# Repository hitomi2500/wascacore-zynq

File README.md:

# wascacore-zynq
Core board module for wasca cartridge, zynq flavour.

Zynq and DDR routing from [`Stanlazy/7z010_ddr`][1].

SODIMM 200 cart edge and board outline from [`Wallbraker/SODIMM`][2].

[1]: https://github.com/Stanlazy/7z010_ddr
[2]: https://github.com/Wallbraker/SODIMM

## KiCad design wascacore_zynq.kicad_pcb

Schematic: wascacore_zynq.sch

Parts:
C1, C2, C21, C23, C42, C43, C44, C45, C46, C47, C48, C49, C51, C52, C53, C54, C56, C57, C58, C59, C60, C61, C62, C63, C64, C65, C66, C67, C68, C69, C70, C71, C72, C73: 0.1uF; C_0603_1608Metric_Pad1.05x0.95mm_HandSolder
C3, C4, C5, C6, C7, C9, C10, C11, C12, C13, C15, C16, C17, C18, C19, C20, C25, C27, C28, C29, C30, C32, C34, C37, C38, C39: C; C_0201_0603Metric
C8, C14, C24, C31, C36, C40, C41: C; C_0402_1005Metric
C22, C26, C33, C35: C; C_0201_0603Metric_WideGap
C50: 10uF; C_1206_HandSoldering
C55: 4.7uF; C_0603_1608Metric_Pad1.05x0.95mm_HandSolder
CN1, CN3: Conn_02x02_Odd_Even; PinHeader_2x02_P2.54mm_Vertical
CN2: Conn_02x05_Odd_Even; Multicomp_MC9A22-1034_2x05_P2.54mm_Horizontal
CN4: Conn_02x03_Odd_Even; PinHeader_2x03_P2.54mm_Vertical
CN5: USB_C_Receptacle_USB2.0; DX07S016JA1R1500
D1: LED_RGB; LED_RGB_5050-6
D2: LED_BCGR; LED_D5.0mm-4_RGB
D3: LED; LED_D3.0mm
D4: BAT54C; SOT-23
IC1: SDRAM_MT48_x16; TSOP-II-54_22.2x10.16mm_P0.8mm
J1: SODIMM-200; SODIMM_DDR2_EDGE
R1: 1K; C_0603_1608Metric_Pad1.05x0.95mm_HandSolder
R2: 0; C_0603_1608Metric_Pad1.08x0.95mm_HandSolder
R3, R4, R17: 10K; C_0603_1608Metric_Pad1.05x0.95mm_HandSolder
R5, R12, R13: 80Ω; R_0201_0603Metric
R6: 4K7Ω; R_0201_0603Metric
R7: 240Ω; R_0201_0603Metric
R8, R9, R10, R11: 470; C_0603_1608Metric_Pad1.08x0.95mm_HandSolder
R14: 470; C_0603_1608Metric_Pad1.05x0.95mm_HandSolder
R15: 5K1; C_0603_1608Metric_Pad1.08x0.95mm_HandSolder
R16: 4K7; C_0603_1608Metric_Pad1.05x0.95mm_HandSolder
RN1, RN2, RN3, RN4, RN5, RN6: 40Ω; R_Array_Convex_4x0402
U1, U2, U5, U6, U7: SN74LVC1T45DBV; SOT-23-6
U3: DDR3; BGA-96_9.0x13.0mm_Layout2x3x16_P0.8mm_NoPaste
U4: xc7z010clg400
U8: LD1117S33TR_SOT223; SOT-223-3_TabPin2

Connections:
/5V: J1.2, J1.4, J1.6, J1.8, J1.10, J1.12
/5V_SATURN_DETECT: R8.2
/+3_3V: C21.1, C23.1, C45.1, C46.1, C47.1, C49.1, C50.1, C51.1, C53.1, C56.1, C57.1, C58.1, C59.1, C60.1, C61.1, C62.1, C63.1, C64.1, C65.1, C66.1, C67.1, C68.1, C69.1, C70.1, C71.1, C72.1, C73.1, CN1.2, CN2.4, CN3.2, CN4.1, IC1.1 (VDD), IC1.3 (VDD), IC1.9 (VDD), IC1.14 (VDD), IC1.27 (VDD), IC1.43 (VDD), IC1.49 (VDD), R3.1, R4.1, U1.1 (VCCA), U2.1 (VCCA), U5.1 (VCCA), U5.5 (DIR), U6.1 (VCCA), U6.5 (DIR), U7.1 (VCCA), U7.5 (DIR), U8.2 (VO); also elsewhere on the board
/+5V_SATURN: C1.1, C2.1, C42.1, C43.1, C44.1, D4.1, R8.1, U1.6 (VCCB), U2.6 (VCCB), U5.6 (VCCB), U6.6 (VCCB), U7.6 (VCCB)
/+5V_SYS: C48.1, CN1.4, D4.3, U8.3 (VI)
/+5V_USB: C52.1, C54.1, C55.1, CN5.A4 (VBUS), CN5.A9 (VBUS), CN5.B4 (VBUS), CN5.B9 (VBUS), D4.2, R16.2
/ABUS_IRQ: U1.4 (B)
/DBG_UART_RX: CN4.5
/DBG_UART_TX: CN4.6
/DDR_VRN: R12.1, U4.G5 (PS_DDR_VRN_502)
/DDR_VRP: R13.1, U4.H5 (PS_DDR_VRP_502)
/DDR_ZQ0: R7.2, U3.L8 (ZQ)
/IBCK: U6.4 (B)
/IBCK_3V: U6.3 (A)
/ILRCK: U7.4 (B)
/ILRCK_3V: U7.3 (A)
/ISD: U5.4 (B)
/ISD_3V: U5.3 (A)
/JTAG_TCK: CN2.1, R1.1
/JTAG_TDI: CN2.9, R4.2
/JTAG_TMS: CN2.5, R3.2
/LED3: D3.2 (A)
/LEDB: R11.1
/LEDG: R10.1
/LEDR: R9.1
/SDR_A0: IC1.23 (A0), U4.D19 (IO_L4P_T0_35)
/SDR_A1: IC1.24 (A1), U4.D20 (IO_L4N_T0_35)
/SDR_A2: IC1.25 (A2), U4.E17 (IO_L3P_T0_DQS_AD1P_35)
/SDR_A3: IC1.26 (A3), U4.D18 (IO_L3N_T0_DQS_AD1N_35)
/SDR_A4: IC1.29 (A4), U4.H17 (IO_L13N_T2_MRCC_35)
/SDR_A5: IC1.30 (A5), U4.H16 (IO_L13P_T2_MRCC_35)
/SDR_A6: IC1.31 (A6), U4.H18 (IO_L14N_T2_AD4N_SRCC_35)
/SDR_A7: IC1.32 (A7), U4.J18 (IO_L14P_T2_AD4P_SRCC_35)
/SDR_A8: IC1.33 (A8), U4.F20 (IO_L15N_T2_DQS_AD12N_35)
/SDR_A9: IC1.34 (A9), U4.F19 (IO_L15P_T2_DQS_AD12P_35)
/SDR_A10: IC1.22 (A10), U4.E19 (IO_L5N_T0_AD9N_35)
/SDR_A11: IC1.35 (A11), U4.G18 (IO_L16N_T2_35)
/SDR_A12: IC1.36 (A12), U4.G17 (IO_L16P_T2_35)
/SDR_BA0: IC1.20 (BA0), U4.F17 (IO_L6N_T0_VREF_35)
/SDR_BA1: IC1.21 (BA1), U4.E18 (IO_L5P_T0_AD9P_35)
/SDR_CAS: IC1.17 (nCAS), U4.M19 (IO_L7P_T1_AD2P_35)
/SDR_CKE: IC1.37 (CKE), U4.L15 (IO_L22N_T3_AD7N_35)
/SDR_CLK: IC1.38 (CLK), U4.N15 (IO_L21P_T3_DQS_AD14P_35)
/SDR_CS: IC1.19 (nCS), U4.F16 (IO_L6P_T0_35)
/SDR_DQ0: IC1.2 (DQ0), U4.K17 (IO_L12P_T1_MRCC_35)
/SDR_DQ1: IC1.4 (DQ1), U4.K18 (IO_L12N_T1_MRCC_35)
/SDR_DQ2: IC1.5 (DQ2), U4.L16 (IO_L11P_T1_SRCC_35)
/SDR_DQ3: IC1.7 (DQ3), U4.L17 (IO_L11N_T1_SRCC_35)
/SDR_DQ4: IC1.8 (DQ4), U4.K19 (IO_L10P_T1_AD11P_35)
/SDR_DQ5: IC1.10 (DQ5), U4.J19 (IO_L10N_T1_AD11N_35)
/SDR_DQ6: IC1.11 (DQ6), U4.L19 (IO_L9P_T1_DQS_AD3P_35)
/SDR_DQ7: IC1.13 (DQ7), U4.L20 (IO_L9N_T1_DQS_AD3N_35)
/SDR_DQ8: IC1.42 (DQ8), U4.K14 (IO_L20P_T3_AD6P_35)
/SDR_DQ9: IC1.44 (DQ9), U4.J14 (IO_L20N_T3_AD6N_35)
/SDR_DQ10: IC1.45 (DQ10), U4.H15 (IO_L19P_T3_35)
/SDR_DQ11: IC1.47 (DQ11), U4.G15 (IO_L19N_T3_VREF_35)
/SDR_DQ12: IC1.48 (DQ12), U4.G19 (IO_L18P_T2_AD13P_35)
/SDR_DQ13: IC1.50 (DQ13), U4.G20 (IO_L18N_T2_AD13N_35)
/SDR_DQ14: IC1.51 (DQ14), U4.J20 (IO_L17P_T2_AD5P_35)
/SDR_DQ15: IC1.53 (DQ15), U4.H20 (IO_L17N_T2_AD5N_35)
/SDR_DQMH: IC1.39 (UDQM-DQMH), U4.N16 (IO_L21N_T3_DQS_AD14N_35)
/SDR_DQML: IC1.15 (LDQM-DQML), U4.M17 (IO_L8P_T1_AD10P_35)
/SDR_RAS: IC1.18 (nRAS), U4.M20 (IO_L7N_T1_AD2N_35)
/SDR_WE: IC1.16 (nWE), U4.M18 (IO_L8N_T1_AD10N_35)
/SSEL: U2.4 (B)
/SWCLK: CN3.3
/SWDIO: CN3.1
/VBUS_SENSE: R16.1, R17.2
DDR_A0: RN4.7 (R2.2), U3.N3 (A0), U4.N2 (PS_DDR_A0_502)
DDR_A1: RN3.8 (R1.2), U3.P7 (A1), U4.K2 (PS_DDR_A1_502)
DDR_A2: RN4.6 (R3.2), U3.P3 (A2), U4.M3 (PS_DDR_A2_502)
DDR_A3: RN2.5 (R4.2), U3.N2 (A3), U4.K3 (PS_DDR_A3_502)
DDR_A4: RN5.6 (R3.2), U3.P8 (A4), U4.M4 (PS_DDR_A4_502)
DDR_A5: RN3.5 (R4.2), U3.P2 (A5), U4.L1 (PS_DDR_A5_502)
DDR_A6: RN4.8 (R1.2), U3.R8 (A6), U4.L4 (PS_DDR_A6_502)
DDR_A7: RN3.6 (R3.2), U3.R2 (A7), U4.K4 (PS_DDR_A7_502)
DDR_A8: RN3.7 (R2.2), U3.T8 (A8), U4.K1 (PS_DDR_A8_502)
DDR_A9: RN1.7 (R2.2), U3.R3 (A9), U4.J4 (PS_DDR_A9_502)
DDR_A10: RN1.5 (R4.2), U3.L7 (A10/AP), U4.F5 (PS_DDR_A10_502)
DDR_A11: RN2.6 (R3.2), U3.R7 (A11), U4.G4 (PS_DDR_A11_502)
DDR_A12: RN2.8 (R1.2), U3.N7 (A12/~BC), U4.E4 (PS_DDR_A12_502)
DDR_A13: RN1.8 (R1.2), U3.T3 (A13), U4.D4 (PS_DDR_A13_502)
DDR_A14: RN2.7 (R2.2), U3.T7 (A14), U4.F4 (PS_DDR_A14_502)
DDR_BA0: RN5.8 (R1.2), U3.M2 (BA0), U4.L5 (PS_DDR_BA0_502)
DDR_BA1: RN6.7 (R2.2), U3.N8 (BA1), U4.R4 (PS_DDR_BA1_502)
DDR_BA2: RN1.6 (R3.2), U3.M3 (BA2), U4.J5 (PS_DDR_BA2_502)
DDR_CK+: R5.1, U3.J7 (CK), U4.L2 (PS_DDR_CKP_502)
DDR_CK-: R5.2, U3.K7 (~CK), U4.M2 (PS_DDR_CKN_502)
DDR_CKE: RN5.7 (R2.2), U3.K9 (CKE), U4.N3 (PS_DDR_CKE_502)
DDR_DQ0: U3.H8 (DQ5), U4.C3 (PS_DDR_DQ0_502)
DDR_DQ1: U3.F2 (DQ2), U4.B3 (PS_DDR_DQ1_502)
DDR_DQ2: U3.G2 (DQ6), U4.A2 (PS_DDR_DQ2_502)
DDR_DQ3: U3.H3 (DQ4), U4.A4 (PS_DDR_DQ3_502)
DDR_DQ4: U3.F7 (DQ1), U4.D3 (PS_DDR_DQ4_502)
DDR_DQ5: U3.E3 (DQ0), U4.D1 (PS_DDR_DQ5_502)
DDR_DQ6: U3.H7 (DQ7), U4.C1 (PS_DDR_DQ6_502)
DDR_DQ7: U3.F8 (DQ3), U4.E1 (PS_DDR_DQ7_502)
DDR_DQ8: U3.C2 (DQ11), U4.E2 (PS_DDR_DQ8_502)
DDR_DQ9: U3.A2 (DQ13), U4.E3 (PS_DDR_DQ9_502)
DDR_DQ10: U3.A3 (DQ15), U4.G3 (PS_DDR_DQ10_502)
DDR_DQ11: U3.C3 (DQ9), U4.H3 (PS_DDR_DQ11_502)
DDR_DQ12: U3.A7 (DQ12), U4.J3 (PS_DDR_DQ12_502)
DDR_DQ13: U3.D7 (DQ8), U4.H2 (PS_DDR_DQ13_502)
DDR_DQ14: U3.B8 (DQ14), U4.H1 (PS_DDR_DQ14_502)
DDR_DQ15: U3.C8 (DQ10), U4.J1 (PS_DDR_DQ15_502)
DDR_DQM0: U3.E7 (LDM), U4.A1 (PS_DDR_DM0_502)
DDR_DQM1: U3.D3 (UDM), U4.F1 (PS_DDR_DM1_502)
DDR_DQS0+: U3.F3 (LDQS), U4.C2 (PS_DDR_DQS_P0_502)
DDR_DQS0-: U3.G3 (~LDQS), U4.B2 (PS_DDR_DQS_N0_502)
DDR_DQS1+: U3.C7 (UDQS), U4.G2 (PS_DDR_DQS_P1_502)
DDR_DQS1-: U3.B7 (~UDQS), U4.F2 (PS_DDR_DQS_N1_502)
DDR_ODT: RN6.6 (R3.2), U3.K1 (ODT), U4.N5 (PS_DDR_ODT_502)
DDR_nCAS: RN6.5 (R4.2), U3.K3 (~CAS), U4.P5 (PS_DDR_CAS_B_502)
DDR_nCS: RN4.5 (R4.2), U3.L2 (~CS), U4.N1 (PS_DDR_CS_B_502)
DDR_nRAS: RN5.5 (R4.2), U3.J3 (~RAS), U4.P4 (PS_DDR_RAS_B_502)
DDR_nRST: R6.1, U3.T2 (~RESET), U4.B4 (PS_DDR_DRST_B_502)
DDR_nWE: RN6.8 (R1.2), U3.L3 (~WE), U4.M5 (PS_DDR_WE_B_502)
GND: C1.2, C2.2, C3.2, C4.2, C5.2, C6.2, C7.2, C8.2, C9.2, C10.2, C11.2, C12.2, C13.2, C14.2, C15.2, C16.2, C17.2, C18.2, C19.2, C20.2, C21.2, C22.2, C23.2, C24.2, C25.2, C26.2, C27.2, C28.2, C29.2, C30.2, C31.2, C32.2, C33.2, C34.2, C35.2, C36.2, C37.2, C38.2, C39.2, C40.2, C41.2, C42.2, C43.2, C44.2, C45.2, C46.2, C47.2, C48.2, C49.2, C50.2, C51.2, C52.2, C53.2, C54.2, C55.2, C56.2, C57.2, C58.2, C59.2, C60.2, C61.2, C62.2, C63.2, C64.2, C65.2, C66.2, C67.2, C68.2, C69.2, C70.2, C71.2, C72.2, C73.2, CN1.1, CN1.3, CN2.2, CN2.10, CN3.4, CN4.2, CN4.4, CN5.A1 (GND), CN5.A12 (GND), CN5.B1 (GND), CN5.B12 (GND), CN5.S1 (SHIELD), D1.1 (RK), D1.2 (GK), D1.3 (BK), D2.2 (K), IC1.6 (GND), IC1.12 (GND), IC1.28 (GND), IC1.41 (GND), IC1.46 (GND), IC1.52 (GND), IC1.54 (GND), J1.1, J1.3, J1.5, J1.7, J1.9, J1.11, J1.39, J1.40, J1.55, J1.56, J1.105, J1.106, J1.107, J1.108, J1.157, J1.158, J1.199, J1.200, R1.2, R6.2, R7.1, R13.2, R14.2, R15.1, R17.1, U1.2 (GND), U2.2 (GND), U2.5 (DIR), U3.A9 (VSS), U3.B1 (VSSQ), U3.B3 (VSS), U3.B9 (VSSQ), U3.D1 (VSSQ), U3.D8 (VSSQ), U3.E1 (VSS), U3.E2 (VSSQ), U3.E8 (VSSQ), U3.F9 (VSSQ), U3.G1 (VSSQ), U3.G8 (VSS), U3.G9 (VSSQ), U3.J2 (VSS), U3.J8 (VSS), U3.M1 (VSS), U3.M9 (VSS), U3.P1 (VSS), U3.P9 (VSS), U3.T1 (VSS), U3.T9 (VSS), U4.A8 (GND[59]), U4.A18 (GND[59]), U4.B1 (GND[59]), U4.B11 (GND[59]), U4.C4 (GND[59]), U4.C9 (GND[59]), U4.C14 (GND[59]), U4.D17 (GND[59]), U4.E10 (GND[59]), U4.E20 (GND[59]), U4.F3 (GND[59]), U4.F7 (GND[59]), U4.G10 (GND[59]), U4.G12 (GND[59]), U4.G16 (GND[59]), U4.H7 (GND[59]), U4.H9 (GND[59]), U4.H11 (GND[59]), U4.H13 (GND[59]), U4.H19 (GND[59]), U4.J2 (GND[59]), U4.J8 (GND[59]), U4.J12 (GND[59]), U4.K5 (GND[59]), U4.K7 (GND[59]), U4.K11 (GND[59]), U4.K13 (GND[59]), U4.K15 (GND[59]), U4.L8 (GND[59]), U4.L12 (GND[59]), U4.L18 (GND[59]), U4.M1 (GND[59]), U4.M7 (GND[59]), U4.M11 (GND[59]), U4.M13 (GND[59]), U4.N4 (GND[59]), U4.N8 (GND[59]), U4.N10 (GND[59]), U4.N12 (GND[59]), U4.N14 (GND[59]), U4.P7 (GND[59]), U4.P9 (GND[59]), U4.P11 (GND[59]), U4.P13 (GND[59]), U4.P17 (GND[59]), U4.R8 (GND[59]), U4.R12 (GND[59]), U4.R20 (GND[59]), U4.T3 (GND[59]), U4.T7 (GND[59]), U4.T13 (GND[59]), U4.U6 (GND[59]), U4.U16 (GND[59]), U4.V9 (GND[59]), U4.V19 (GND[59]), U4.W2 (GND[59]), U4.W12 (GND[59]), U4.Y5 (GND[59]), U4.Y15 (GND[59]), U5.2 (GND), U6.2 (GND), U7.2 (GND), U8.1 (GND); also elsewhere on the board
unnamed: CN5.A5 (CC1), CN5.B5 (CC2), R15.2
unnamed: CN5.A6 (D+), CN5.B6 (D+)
unnamed: CN5.A7 (D-), CN5.B7 (D-)
unnamed: D1.4 (BA), D2.1 (BA), R11.2
unnamed: D1.5 (GA), D2.3 (GA), R10.2
unnamed: D1.6 (RA), D2.4 (RA), R9.2
unnamed: D3.1 (K), R14.1
unnamed: R2.2, U2.3 (A)
unnamed: U4.A13 (VCCO_MIO1_501[4]), U4.B16 (VCCO_MIO1_501[4]), U4.D12 (VCCO_MIO1_501[4]), U4.E15 (VCCO_MIO1_501[4])
unnamed: U4.B6 (VCCO_MIO0_500[2]), U4.D7 (VCCO_MIO0_500[2])
unnamed: U4.F8 (VCCPAUX[5]), U4.G9 (VCCPAUX[5]), U4.H8 (VCCPAUX[5]), U4.K8 (VCCPAUX[5]), U4.M8 (VCCPAUX[5])
unnamed: U4.G7 (VCCPINT[6]), U4.J7 (VCCPINT[6]), U4.L7 (VCCPINT[6]), U4.N7 (VCCPINT[6]), U4.P8 (VCCPINT[6]), U4.R7 (VCCPINT[6])
unnamed: U4.G11 (VCCBRAM[2]), U4.H10 (VCCBRAM[2])
unnamed: U4.G13 (VCCINT[9]), U4.H12 (VCCINT[9]), U4.J13 (VCCINT[9]), U4.K12 (VCCINT[9]), U4.L13 (VCCINT[9]), U4.M12 (VCCINT[9]), U4.N13 (VCCINT[9]), U4.P12 (VCCINT[9]), U4.R13 (VCCINT[9])
unnamed: U4.J11 (VCCAUX[6]), U4.L11 (VCCAUX[6]), U4.N9 (VCCAUX[6]), U4.N11 (VCCAUX[6]), U4.P10 (VCCAUX[6]), U4.R9 (VCCAUX[6])
unnamed: U4.T8 (VCCO_13[4]), U4.U11 (VCCO_13[4]), U4.W7 (VCCO_13[4]), U4.Y10 (VCCO_13[4])
VCC_DDR: C4.1, C5.1, C6.1, C7.1, C9.1, C10.1, C12.1, C13.1, C15.1, C16.1, C17.1, C18.1, C20.1, C22.1, C25.1, C26.1, C28.1, C30.1, C33.1, C35.1, R12.2, U3.A1 (VDDQ), U3.A8 (VDDQ), U3.B2 (VDD), U3.C1 (VDDQ), U3.C9 (VDDQ), U3.D2 (VDDQ), U3.D9 (VDD), U3.E9 (VDDQ), U3.F1 (VDDQ), U3.G7 (VDD), U3.H2 (VDDQ), U3.H9 (VDDQ), U3.K2 (VDD), U3.K8 (VDD), U3.N1 (VDD), U3.N9 (VDD), U3.R1 (VDD), U3.R9 (VDD), U4.A3 (VCCO_DDR_502[10]), U4.D2 (VCCO_DDR_502[10]), U4.E5 (VCCO_DDR_502[10]), U4.G1 (VCCO_DDR_502[10]), U4.H4 (VCCO_DDR_502[10]), U4.L3 (VCCO_DDR_502[10]), U4.P2 (VCCO_DDR_502[10]), U4.R5 (VCCO_DDR_502[10]), U4.U1 (VCCO_DDR_502[10]), U4.V4 (VCCO_DDR_502[10])
VREF_DDR: C29.1, C32.1, C37.1, C38.1, C40.1, U3.H1 (VREFDQ), U3.M8 (VREFCA), U4.H6 (PS_DDR_VREF0_502), U4.P6 (PS_DDR_VREF1_502)
VTT_DDR: C3.1, C8.1, C11.1, C14.1, C19.1, C24.1, C27.1, C31.1, C34.1, C36.1, C39.1, C41.1, RN1.1 (R1.1), RN1.2 (R2.1), RN1.3 (R3.1), RN1.4 (R4.1), RN2.1 (R1.1), RN2.2 (R2.1), RN2.3 (R3.1), RN2.4 (R4.1), RN3.1 (R1.1), RN3.2 (R2.1), RN3.3 (R3.1), RN3.4 (R4.1), RN4.1 (R1.1), RN4.2 (R2.1), RN4.3 (R3.1), RN4.4 (R4.1), RN5.1 (R1.1), RN5.2 (R2.1), RN5.3 (R3.1), RN5.4 (R4.1), RN6.1 (R1.1), RN6.2 (R2.1), RN6.3 (R3.1), RN6.4 (R4.1)

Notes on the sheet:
There are 3 power rails VTT_DDR VREF_DDR VCC_DDR
External 5V power supply + 3V3 power output/check
SDRAM : shares 3V3 with MAX10 DDR : requires 2V5 power supply
ONLY 1 OF THE RGB LEDS SHOULD BE PLACED
Compatible connectors: JAE DX07S016JA1R1500 JAE DX07S016JA3R1500 HROPARTS TYPE-C-31-M-12 HROPARTS TYPE-C-31-M-14 XKB U262-161N-4BVC11 Jing Ext. C167321
5V Tolerant pin

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
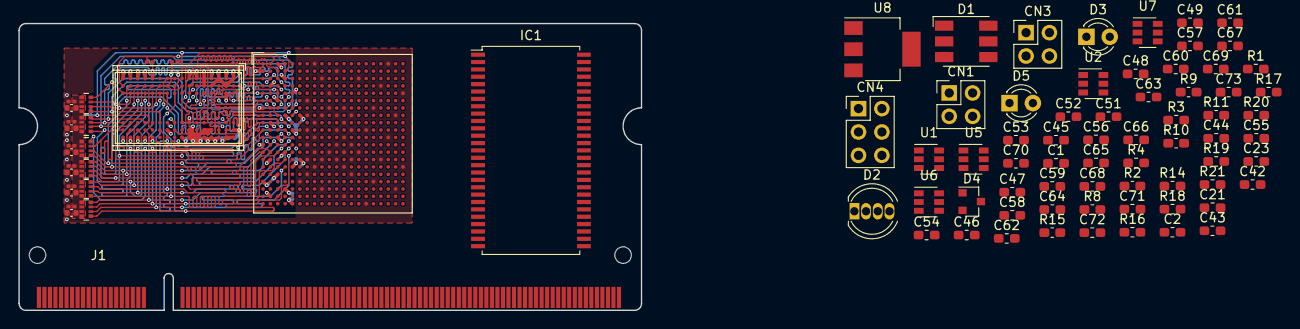
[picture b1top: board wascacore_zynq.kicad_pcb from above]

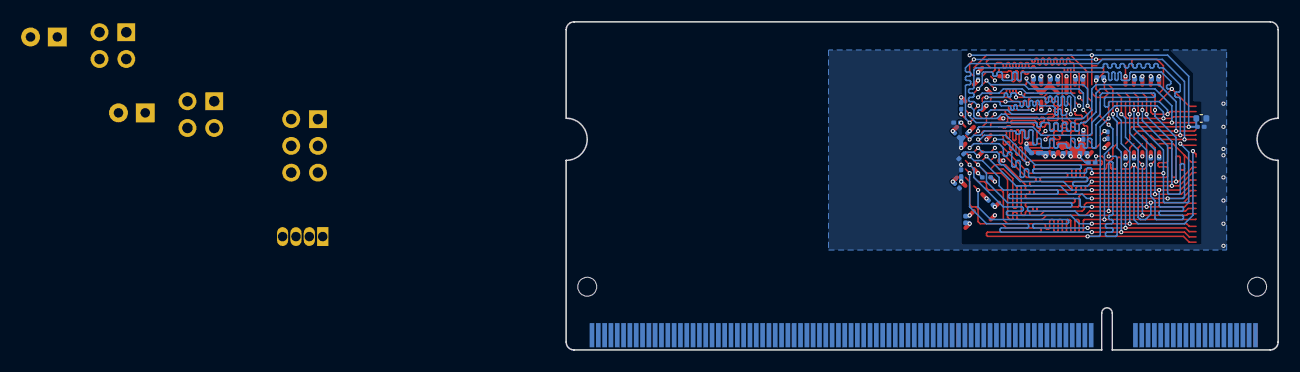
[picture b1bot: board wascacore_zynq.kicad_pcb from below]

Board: 4 copper layers, 67.6 x 31.2 mm, 117 parts (28 on the bottom side), 118 nets.

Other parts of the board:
D5: LED; LED_D3.0mm
R18: 470; C_0603_1608Metric_Pad1.05x0.95mm_HandSolder
R19, R20, R21: 10K; C_0603_1608Metric_Pad1.05x0.95mm_HandSolder

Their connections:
/+3_3V: R19.1, R20.1, R21.1; also elsewhere on the board
GND: R18.2; also elsewhere on the board
unnamed: D5.1, R18.1

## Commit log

2021-12-16 Submodule update
2021-12-16 Components and layout import
2021-12-16 Readme update
2021-12-16 SDRAM added
2021-12-24 Routing from wasca board

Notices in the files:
wascacore_zynq.kicad_pcb:
GPL
